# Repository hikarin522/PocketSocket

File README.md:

# electron-skeleton
skeleton for electron

###usage
```
$ npm install
$ cd ./app
$ npm install
$ cd ../
$ npm start
```

###package
```
$ gulp
```

###lib etc...
- [Electron](http://electron.atom.io/)
- [electron-compile](https://github.com/electronjs/electron-compile)
- [electron-edge](https://github.com/kexplo/electron-edge)
- [RxJS](http://reactivex.io/)
- [Cycle.js](http://cycle.js.org/)
- [jQuery](https://jquery.com/)
- [Bootstrap](http://getbootstrap.com/)

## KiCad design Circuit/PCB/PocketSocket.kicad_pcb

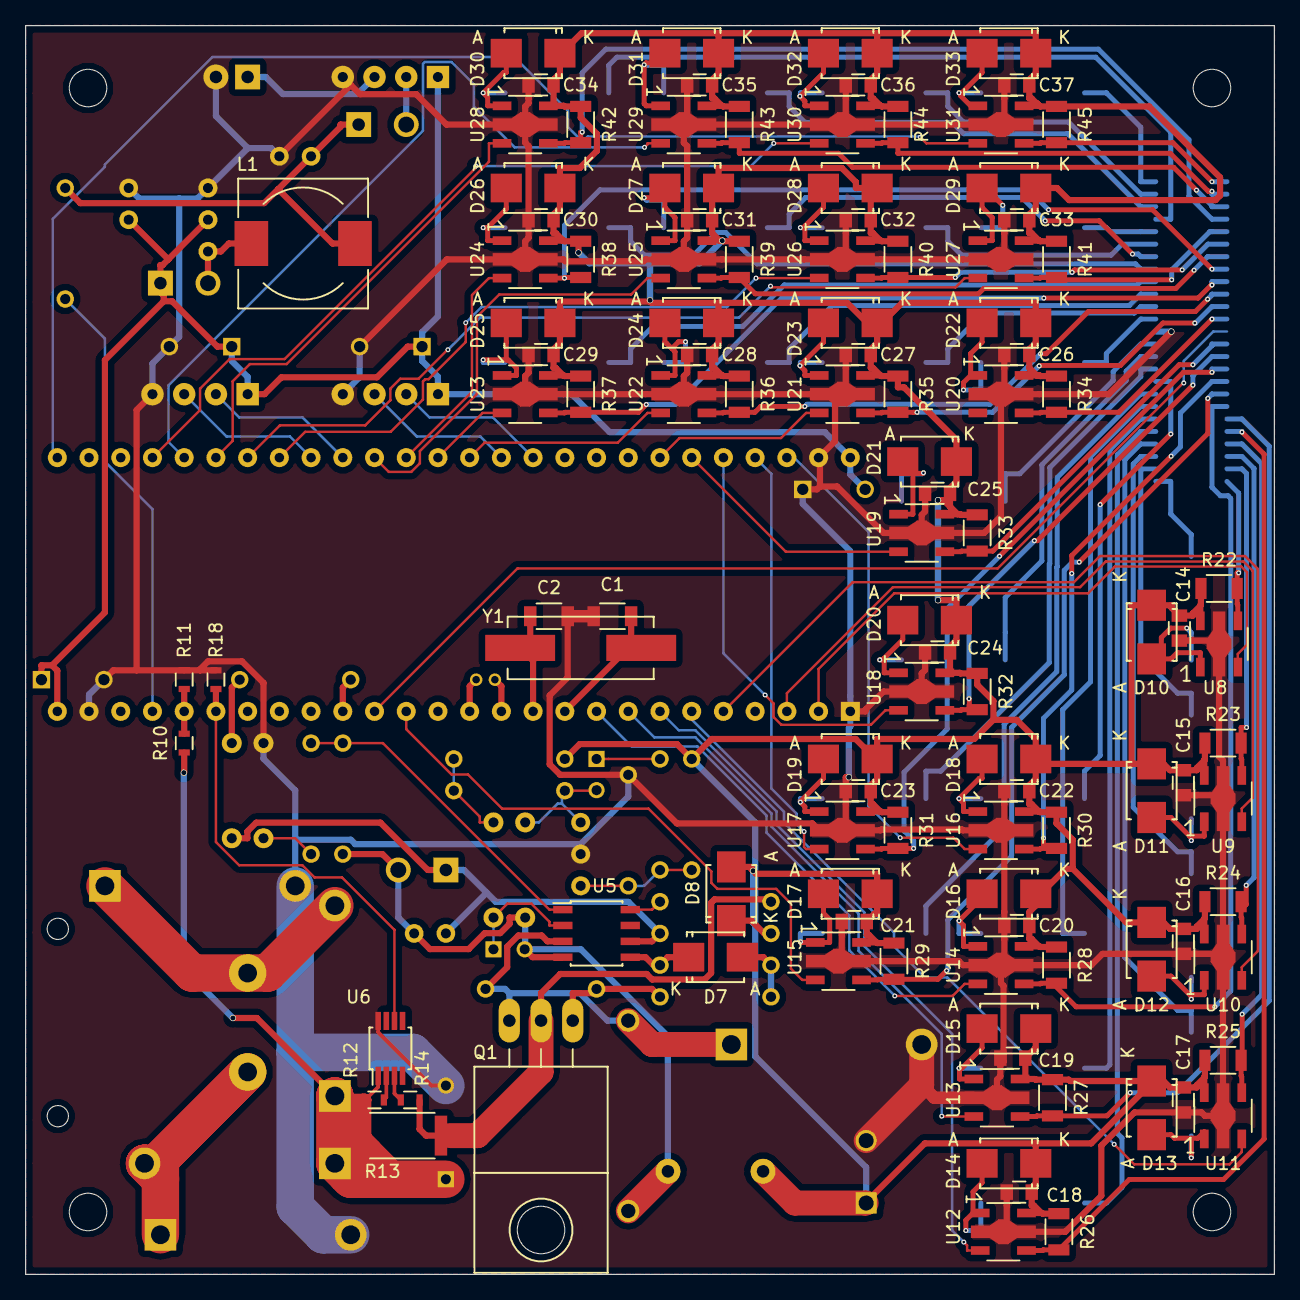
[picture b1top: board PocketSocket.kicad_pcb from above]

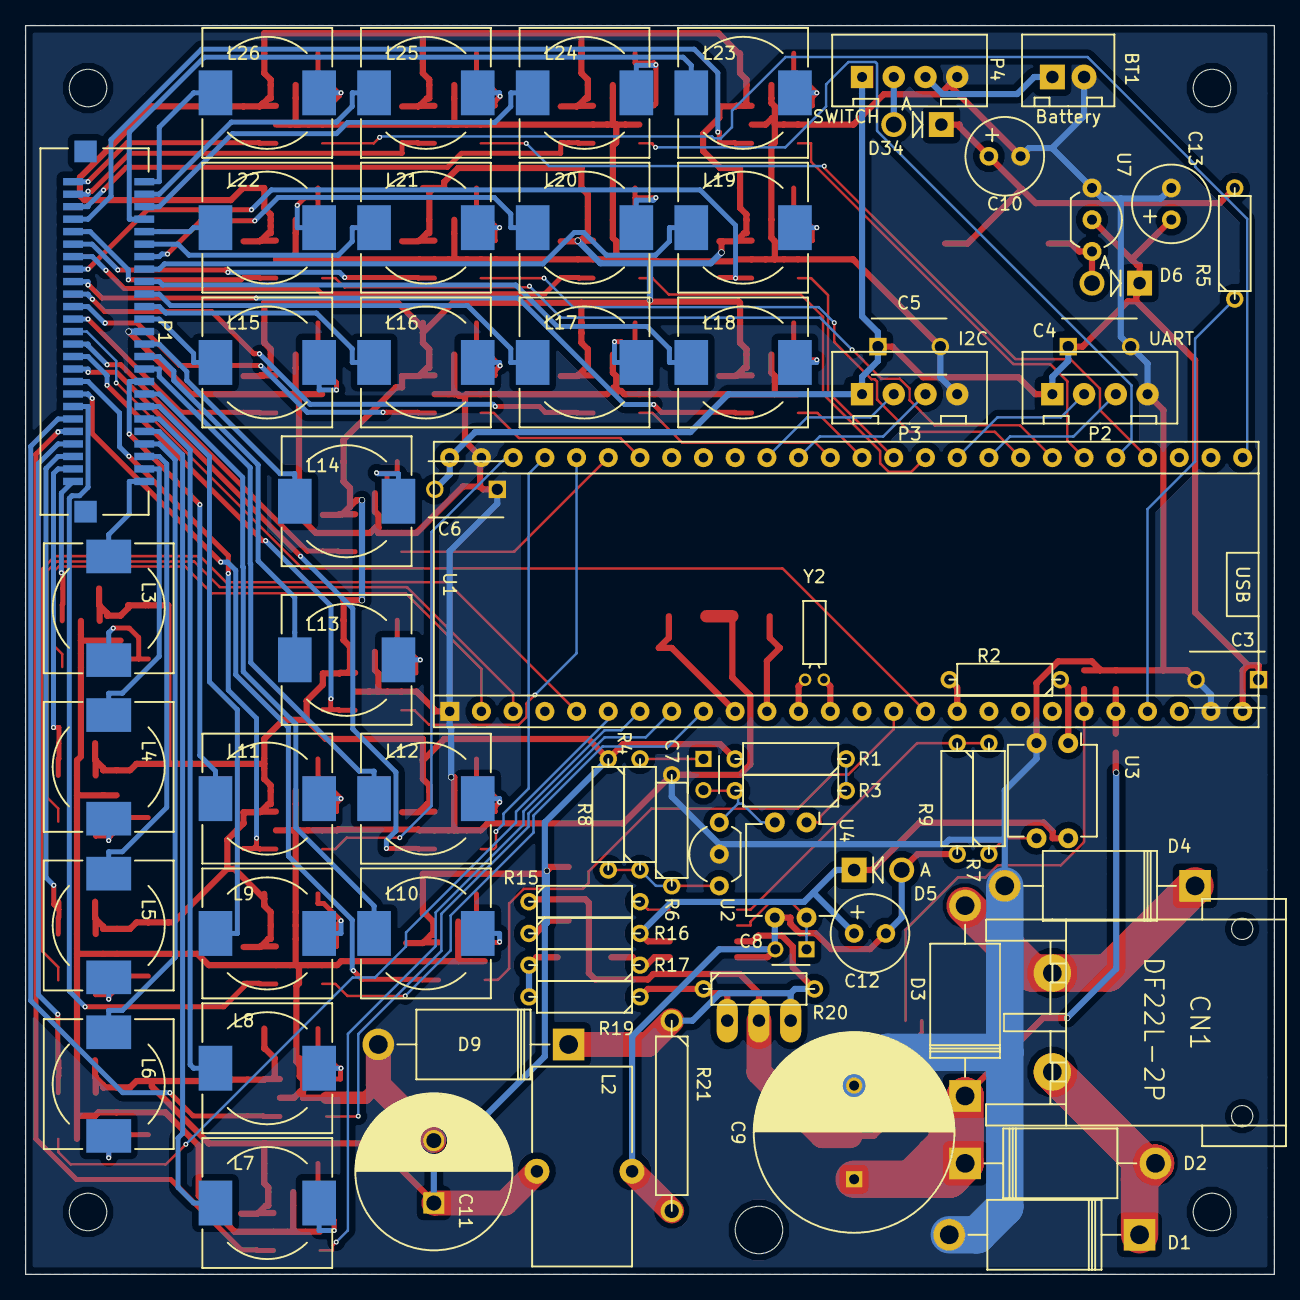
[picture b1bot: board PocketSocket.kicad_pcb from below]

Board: 2 copper layers, 100.0 x 100.0 mm, 182 parts (71 on the bottom side), 137 nets.

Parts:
BT1: Battery; B2B-XH-A
C1, C2: 12p; C_1206
C3, C4, C5, C6: 1u; C_Disc_D6_P5
C7: 0.1u; C_Disc_D3_P2.5
C8: 0.01u; C_Disc_D3_P2.5
C9: 100u; C_Radial_D16_L25_P7.5
C10: 47u; Elko_vert_11.2x6.3mm_RM2.5_CopperClear
C11: 470u; C_Radial_D12.5_L25_P5
C12: 10u; Elko_vert_11.2x6.3mm_RM2.5_CopperClear
C13: 22u; Elko_vert_11.2x6.3mm_RM2.5_CopperClear
C14, C15, C16, C17, C18, C19, C20, C21, C22, C23, C25, C26, C27, C28, C29, C30, C31, C32, C33, C34, C35, C36, C37: C_0805
C24: 4.7u; C_0805
CN1: DF22L-2P; CONN_RED_2P
D1, D2, D3, D4, D9: ER504; Diode_DO-201AD_Horizontal_RM15
D5: 24V; Diode_DO-41_SOD81_Vertical_AnodeUp
D6, D34: 1S4; Diode_DO-41_SOD81_Vertical_AnodeUp
D7, D10, D11, D12, D13, D20: D1FS4A; SMB_Standard
D8: ES1D; SMB_Standard
D14, D15, D16, D17, D18, D19, D21, D22, D23, D24, D25, D26, D27, D28, D29, D30, D31, D32, D33: SMB_Standard
L1: 100u; Choke_SMD_10.4x10.4_H4.8
L2: 100u; Choke_Toroid_8x16mm_Vertical
L3, L4, L5, L6, L7, L8, L9, L10, L11, L12, L13, L14, L15, L16, L17, L18, L19, L20, L21, L22, L23, L24, L25, L26: 68u; Choke_SMD_10.4x10.4_H4.8
P1: CONN_02X25; DF50-50DP-1H
P2: UART; B4B-XH-A
P3: I2C; B4B-XH-A
P4: SWITCH; B4B-XH-A
Q1: RCX080N25; TO-220_Neutral123_Horizontal_LargePads
R1: 2k; R3-5
R2, R3, R4, R16: 1k; R3-5
R5, R6: 10k; R3-5
R7: 75k; R3-5
R8: 120k; R3-5
R9: 15k; R3-5
R10: 180k; R_0603
R11: 6.2k; R_0603
R12: 2.7k; R_0603
R13: 0.27; R_2512
R14, R18: 27k; R_0603
R15: 6.8k; R3-5
R17: 150; R3-5
R19: 10; R3-5
R20: 100k; R3-5
R21: 0.1; R6
R22, R23, R24, R25, R32: 0.27; R_1206
R26, R27, R28, R29, R30, R31, R33, R34, R35, R36, R37, R38, R39, R40, R41, R42, R43, R44, R45: R_1206
U1: CY8CKIT-059_Target; CY8KIT-059_Target
U2: TL431; TO-92_Inline_Wide
U3, U4: PC817; DIP-4_W7.62mm
U5: BM1P061FJ; SOIC-8_3.9x4.9mm_Pitch1.27mm
U6: HV7802; MSOP-8_3x3mm_Pitch0.65mm
U7: HT7750A; TO-92_Inline_Wide
U8, U9, U10, U11, U18: CL6807; SOT89-5_Housing
U12, U13, U14, U15, U16, U17, U19, U20, U21, U22, U23, U24, U25, U26, U27, U28, U29, U30, U31: SOT89-5_Housing
Y1: 24.576M; Crystal_HC49-SD_SMD
Y2: 32.768k; Crystal_Round_Horizontal_2mm

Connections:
+5V: C3.1, C4.1, C5.1, C6.2, C13.1, D6.1, P2.1, P3.1, P4.1, U1.26, U1.52, U7.2
/LED_DRIVER_0/LEDA: P1.2, R22.2, U8.4
/LED_DRIVER_0/LEDC: L3.2, P1.1
/LED_DRIVER_0/PWM: U1.2, U8.3
/LED_DRIVER_1/LEDA: P1.4, R23.2, U9.4
/LED_DRIVER_1/LEDC: L4.2, P1.3
/LED_DRIVER_1/PWM: U1.3, U9.3
/LED_DRIVER_2/LEDA: P1.6, R24.2, U10.4
/LED_DRIVER_2/LEDC: L5.2, P1.5
/LED_DRIVER_2/PWM: U1.5, U10.3
/LED_DRIVER_3/LEDA: P1.8, R25.2, U11.4
/LED_DRIVER_3/LEDC: L6.2, P1.7
/LED_DRIVER_3/PWM: U1.6, U11.3
/LED_DRIVER_4/LEDA: P1.10, R26.2, U12.4
/LED_DRIVER_4/LEDC: L7.2, P1.9
/LED_DRIVER_4/PWM: U1.7, U12.3
/LED_DRIVER_5/LEDA: P1.12, R27.2, U13.4
/LED_DRIVER_5/LEDC: L8.2, P1.11
/LED_DRIVER_5/PWM: U1.8, U13.3
/LED_DRIVER_6/LEDA: P1.14, R28.2, U14.4
/LED_DRIVER_6/LEDC: L9.2, P1.13
/LED_DRIVER_6/PWM: U1.9, U14.3
/LED_DRIVER_7/LEDA: P1.16, R29.2, U15.4
/LED_DRIVER_7/LEDC: L10.2, P1.15
/LED_DRIVER_7/PWM: U1.15, U15.3
/LED_DRIVER_8/LEDA: P1.18, R30.2, U16.4
/LED_DRIVER_8/LEDC: L11.2, P1.17
/LED_DRIVER_8/PWM: U1.50, U16.3
/LED_DRIVER_9/LEDA: P1.20, R31.2, U17.4
/LED_DRIVER_9/LEDC: L12.2, P1.19
/LED_DRIVER_9/PWM: U1.49, U17.3
/LED_DRIVER_10/LEDA: P1.22, R32.2, U18.4
/LED_DRIVER_10/LEDC: L13.2, P1.21
/LED_DRIVER_10/PWM: U1.48, U18.3
/LED_DRIVER_11/LEDA: P1.24, R33.2, U19.4
/LED_DRIVER_11/LEDC: L14.2, P1.23
/LED_DRIVER_11/PWM: U1.47, U19.3
/LED_DRIVER_12/LEDA: P1.28, R34.2, U20.4
/LED_DRIVER_12/LEDC: L15.2, P1.27
/LED_DRIVER_13/LEDA: P1.30, R35.2, U21.4
/LED_DRIVER_13/LEDC: L16.2, P1.29
/LED_DRIVER_13/PWM: U1.46, U21.3
/LED_DRIVER_14/LEDA: P1.32, R36.2, U22.4
/LED_DRIVER_14/LEDC: L17.2, P1.31
/LED_DRIVER_14/PWM: U1.40, U22.3
/LED_DRIVER_15/LEDA: P1.34, R37.2, U23.4
/LED_DRIVER_15/LEDC: L18.2, P1.33
/LED_DRIVER_15/PWM: U1.39, U23.3
/LED_DRIVER_16/LEDA: P1.36, R38.2, U24.4
/LED_DRIVER_16/LEDC: L19.2, P1.35
/LED_DRIVER_16/PWM: U1.38, U24.3
/LED_DRIVER_17/LEDA: P1.38, R39.2, U25.4
/LED_DRIVER_17/LEDC: L20.2, P1.37
/LED_DRIVER_17/PWM: U1.37, U25.3
/LED_DRIVER_18/LEDA: P1.40, R40.2, U26.4
/LED_DRIVER_18/LEDC: L21.2, P1.39
/LED_DRIVER_18/PWM: U1.34, U26.3
/LED_DRIVER_19/LEDA: P1.42, R41.2, U27.4
/LED_DRIVER_19/LEDC: L22.2, P1.41
/LED_DRIVER_19/PWM: U1.33, U27.3
/LED_DRIVER_20/LEDA: P1.44, R42.2, U28.4
/LED_DRIVER_20/LEDC: L23.2, P1.43
/LED_DRIVER_20/PWM: U1.32, U28.3
/LED_DRIVER_21/LEDA: P1.46, R43.2, U29.4
/LED_DRIVER_21/LEDC: L24.2, P1.45
/LED_DRIVER_21/PWM: U1.31, U29.3
/LED_DRIVER_22/LEDA: P1.48, R44.2, U30.4
/LED_DRIVER_22/LEDC: L25.2, P1.47
/LED_DRIVER_22/PWM: U1.30, U30.3
/LED_DRIVER_23/LEDA: P1.50, R45.2, U31.4
/LED_DRIVER_23/LEDC: L26.2, P1.49
/LED_DRIVER_23/PWM: U1.27, U31.3
/PowerInput/BatteryCheck: R5.1, U1.23
/PowerInput/EN: R2.2, U1.17
/PowerInput/Isense: R18.1, U1.21, U6.6
/PowerInput/Vsense: R10.2, R11.1, U1.22
/RX: P2.2, U1.36
/SCL: P3.2, U1.42
/SDA: P3.3, U1.41
/TX: P2.3, U1.35
GND: BT1.2, C1.2, C2.2, C3.2, C4.2, C5.2, C6.1, C9.2, C10.2, C11.2, C13.2, C14.2, C15.2, C16.2, C17.2, C18.2, C19.2, C20.2, C21.2, C22.2, C23.2, C24.2, C25.2, C26.2, C27.2, C28.2, C29.2, C30.2, C31.2, C32.2, C33.2, C34.2, C35.2, C36.2, C37.2, D2.2, D4.2, D9.2, P1.25, P2.4, P3.4, P4.4, R6.2, R11.2, R18.2, U1.1, U1.25, U1.51, U2.2, U3.2, U6.8, U7.1, U8.2, U9.2, U10.2, U11.2, U12.2, U13.2, U14.2, U15.2, U16.2, U17.2, U18.2, U19.2, U20.2, U21.2, U22.2, U23.2, U24.2, U25.2, U26.2, U27.2, U28.2, U29.2, U30.2, U31.2
unnamed: BT1.1, P4.3
unnamed: C1.1, U1.10, Y1.1
unnamed: C2.1, U1.11, Y1.2
unnamed: C7.1, R4.2
unnamed: C7.2, R3.2, U2.3, U4.2
unnamed: C8.1, U4.4, U5.2
unnamed: C9.1, D1.1, D3.1, R10.1, R12.1, R13.2, U6.1
unnamed: C10.1, D34.1, L1.2, R5.2
unnamed: C12.1, D5.1, R16.2, U3.4, U5.6
unnamed: C8.2, C12.2, D5.2, L2.1, R9.2, R21.2, U4.3, U5.4
unnamed: CN1.1, D1.2, D2.1
unnamed: CN1.2, D3.2, D4.1
unnamed: D6.2, L1.1, U7.3
unnamed: D7.1, R17.1, U5.5
unnamed: D7.2, R17.2, R19.2
unnamed: D8.1, R16.1
unnamed: D9.1, Q1.3, R20.2, R21.1, U5.3
unnamed: D10.2, L3.1, U8.1
unnamed: D11.2, L4.1, U9.1
unnamed: D12.2, L5.1, U10.1
unnamed: D13.2, L6.1, U11.1
unnamed: D14.2, L7.1, U12.1
unnamed: D15.2, L8.1, U13.1
unnamed: D16.2, L9.1, U14.1
unnamed: D17.2, L10.1, U15.1
unnamed: D18.2, L11.1, U16.1
unnamed: D19.2, L12.1, U17.1
unnamed: D20.2, L13.1, U18.1
unnamed: D21.2, L14.1, U19.1
unnamed: D22.2, L15.1, U20.1
unnamed: D23.2, L16.1, U21.1
unnamed: D24.2, L17.1, U22.1
unnamed: D25.2, L18.1, U23.1
unnamed: D26.2, L19.1, U24.1
unnamed: D27.2, L20.1, U25.1
unnamed: D28.2, L21.1, U26.1
unnamed: D29.2, L22.1, U27.1
unnamed: D30.2, L23.1, U28.1
unnamed: D31.2, L24.1, U29.1
unnamed: D32.2, L25.1, U30.1
unnamed: D33.2, L26.1, U31.1
unnamed: D34.2, P4.2
unnamed: P1.26, U1.16
unnamed: Q1.1, R19.1, R20.1
unnamed: Q1.2, R13.1, R14.2, R15.1
unnamed: R1.1, R3.1, U4.1
unnamed: R2.1, U3.1
unnamed: R4.1, R6.1, R8.2, U2.1
unnamed: R7.1, U3.3
unnamed: R7.2, R9.1, U5.1
unnamed: R12.2, U6.2
unnamed: R14.1, U6.3
unnamed: R15.2, U5.8
unnamed: U1.12, Y2.1
unnamed: U1.13, Y2.2
VCC: C11.1, C14.1, C15.1, C16.1, C17.1, C18.1, C19.1, C20.1, C21.1, C22.1, C23.1, C24.1, C25.1, C26.1, C27.1, C28.1, C29.1, C30.1, C31.1, C32.1, C33.1, C34.1, C35.1, C36.1, C37.1, D8.2, D10.1, D11.1, D12.1, D13.1, D14.1, D15.1, D16.1, D17.1, D18.1, D19.1, D20.1, D21.1, D22.1, D23.1, D24.1, D25.1, D26.1, D27.1, D28.1, D29.1, D30.1, D31.1, D32.1, D33.1, L2.2, R1.2, R8.1, R22.1, R23.1, R24.1, R25.1, R26.1, R27.1, R28.1, R29.1, R30.1, R31.1, R32.1, R33.1, R34.1, R35.1, R36.1, R37.1, R38.1, R39.1, R40.1, R41.1, R42.1, R43.1, R44.1, R45.1, U8.5, U9.5, U10.5, U11.5, U12.5, U13.5, U14.5, U15.5, U16.5, U17.5, U18.5, U19.5, U20.5, U21.5, U22.5, U23.5, U24.5, U25.5, U26.5, U27.5, U28.5, U29.5, U30.5, U31.5

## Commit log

2015-09-03 add gitattributes
2015-09-03 add PartsList
2015-09-03 add KiCad
2015-09-03 Squashed 'Circuit/KiCad/Components/' content from commit 1487ee7
    git-subtree-dir: Circuit/KiCad/Components
    git-subtree-split: 1487ee720c6754a30e0cd2a8bf039fbbe2071041
2015-09-03 update gitignore
2015-09-03 add HV7802
2015-09-03 add BM1PxxxFJ
2015-09-03 remove *.bck
2015-09-03 add DataSheets
2015-09-03 add PowerInput
2015-09-07 add CL6807
2015-09-07 add TL431
2015-09-07 add data sheets
2015-09-07 add LED driver
2015-09-09 EeSchema settled
2015-09-09 rename directory
2015-09-09 Squashed 'Circuit/PCB/lib/' content from commit cf39b9e
    git-subtree-dir: Circuit/PCB/lib
    git-subtree-split: cf39b9e3961c8c571407d2293b4a07b801ee716f
2015-09-09 add footprint
2015-09-09 change lib
2015-09-10 add datasheet
2015-09-10 add DF50-50DP
2015-09-10 add footprint CY8KIT-059 Target
2015-09-10 CvPcb settled
2015-09-10 Squashed 'Circuit/PCB/lib/' changes from cf39b9e..a132eb7
    a132eb7 add footprint CY8KIT-059 Target
    0506353 add DF50-50DP
    651e4a9 add footprint
    git-subtree-dir: Circuit/PCB/lib
    git-subtree-split: a132eb78cc8b1a036124a23d916cd31fff6da6ea
2015-09-10 update footprint
2015-09-10 update PCB
2015-09-15 update pcb layout
2015-09-16 add gerber
2015-11-10 add harness
2015-11-10 add psoc project
2015-11-10 Squashed 'Software/Electron/' content from commit 46aab75
    git-subtree-dir: Software/Electron
    git-subtree-split: 46aab75bb86fb369259cf1aaba7352a9ee304c7b
2015-11-10 set project name
2015-11-10 update layout
2015-11-13 add bypass
2015-11-20 update edgeSerialPort
2015-11-20 add portInfoDriver
2015-11-23 chage react
2015-11-25 update packages
2015-11-27 update main
2015-12-10 add components
2015-12-11 add LPF Component
2015-12-14 dma fix
2015-12-17 dma update
2015-12-18 update pwm_control
2015-12-21 test
2015-12-21 update package
